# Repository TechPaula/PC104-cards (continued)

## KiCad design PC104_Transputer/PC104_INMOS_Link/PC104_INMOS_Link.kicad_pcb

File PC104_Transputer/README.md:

# PC104 Transputer card

This is a PC104plus board that provides a connection to an INMOS C011 and on to a transputer.
This is going to form the basis of a PC104 stack of transputers.

The PCI connector is not connected and is not needed, it is there so that should I get any PCI cards in the future I can use them on my system

TLDR; Currently none of these are proven beyond loopback tests

## Updates

2025-09-07 - Well the previous card had some issues, mostly around the address decoding as far as I can tell, so I made a new card with just the C011 on and added more of the ISA lines to the CPLD. This now behaves with both of my PC104 computers (the previous one would cause one of them to fail to boot). However all 4 of my TRAMs now seem to have stopped working :( The C011 link card does at least now perform loopback tests perfectly. The other thing I've done is cut the track from the ISA 14.3MHz clock and used the 8MHz bus clock. I need to update the schematics and PCB 

2025-07-19 - OMG, so much work... CPLD files updated and fixed a couple of errors. I can now write and read from 0x150 to 0x153 as expected. I can now also write to 0x160 & 0x161 as expected and get the behaviours expected. But when you read from 0x160 you got the wrong value and from then on when you read from 0x153 (output status) returns 0, so the output has not been sent/acknowledged by the TRAM.

### Some useful things I've discovered along the way;
* write a 1 to 0x160 Asserts reset, writing a 0 deasserts it.
* Write a 1 to 0x161 to asset Analyse, writing a 0 deasserts it
* Write a 0 to 0x152 to clear INPUT interrupt enable (unless you plan to use interrupts)
* Write a 0 to 0x152 to clear OUTPUT interrupt enable (unless you plan to use interrupts)
* READ from 0x152 to get the input status (if bit0 is 0 then there is no Data waiting)
* READ from 0x160 to get the error stats (if bit 0 is 0 then there is no error)
* Write to 0x151 to send data into the C011/TRAM.
* READ from 0x150 to receive data from the C011/TRAM

2025-07-11 - Spotted another mistake, I had the Databus reversed. I also added the CPLD files I've programmed and tested.

2025-07-09 - Spotted a major mistake with the CPLD, the board needs a redesign as it has the wrong pin out!

2025-07-06 - Fixed a few minor issues with both boards & added image of Dual TRAM board

2025-07-06 - Added TRAM model

2025-07-05 - Board routed but NOT yet built/tested, the code for the CPLD is not not written.

## License
There isn't one, if you want to build it or adapt it, go for it.
I offer no warranty, nor will I accept any responsiblity for damage to you or your equipment

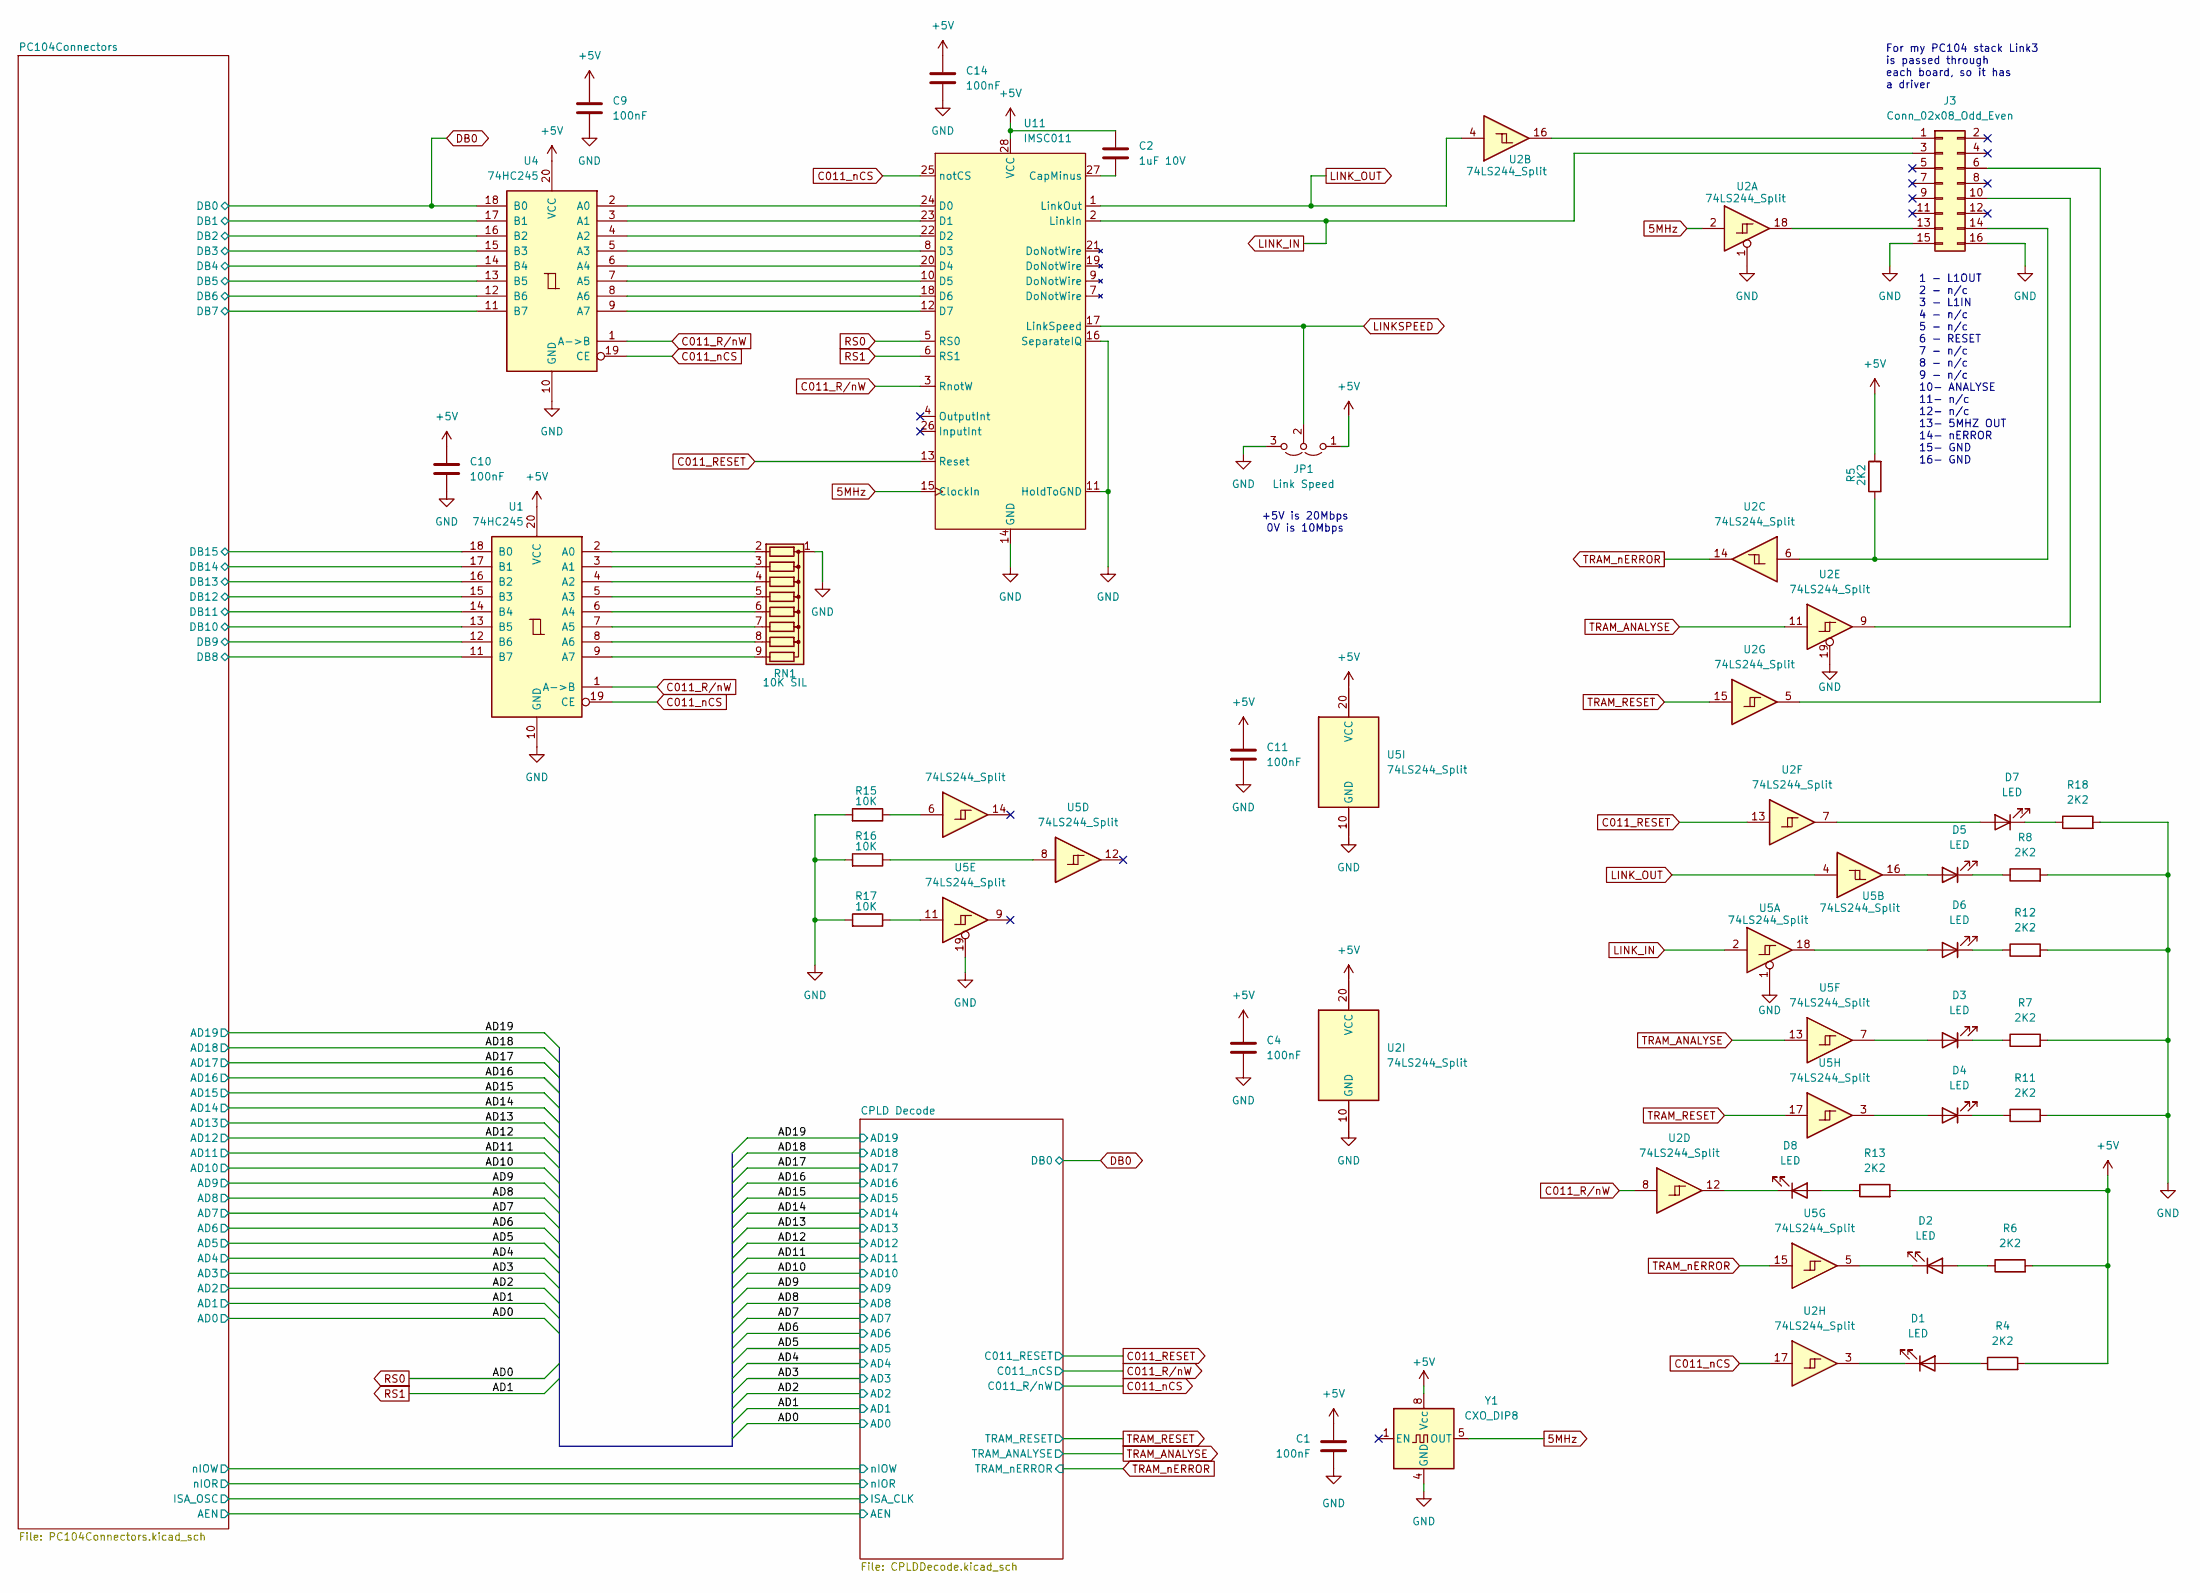
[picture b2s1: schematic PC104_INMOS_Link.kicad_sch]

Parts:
C1, C4, C9, C10, C11, C14: 100nF; C_0805_2012Metric
C2: 1uF 10V; C_0805_2012Metric
D1, D2, D3, D4, D5, D6, D7, D8: LED; LED_0603_1608Metric
J3: Conn_02x08_Odd_Even; PinHeader_2x08_P2.54mm_Horizontal
JP1: Link Speed; PinHeader_1x03_P2.54mm_Vertical
R4, R5, R6, R7, R8, R11, R12, R13, R18: 2K2; R_0603_1608Metric
R15, R16, R17: 10K; R_0603_1608Metric
RN1: 10K SIL; R_Array_SIP9
U1, U4: 74HC245; DIP-20_W7.62mm_Socket
U2, U5: 74LS244_Split; DIP-20_W7.62mm_Socket
U11: IMSC011; DIP-28_W15.24mm
Y1: CXO_DIP8; Oscillator_DIP-8

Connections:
5MHz: U2.2, U11.15 (ClockIn), Y1.5 (OUT)
+5V: C1.1, C2.1, C4.1, C9.1, C10.1, C11.1, C14.1, JP1.1 (A), R4.2, R5.2, R6.2, R13.2, U1.20 (VCC), U2.20 (VCC), U4.20 (VCC), U5.20 (VCC), U11.28 (VCC), Y1.8 (Vcc); also elsewhere on the board
/PC104Connectors/DB1: U4.17 (B1); also elsewhere on the board
/PC104Connectors/DB2: U4.16 (B2); also elsewhere on the board
/PC104Connectors/DB3: U4.15 (B3); also elsewhere on the board
/PC104Connectors/DB4: U4.14 (B4); also elsewhere on the board
/PC104Connectors/DB5: U4.13 (B5); also elsewhere on the board
/PC104Connectors/DB6: U4.12 (B6); also elsewhere on the board
/PC104Connectors/DB7: U4.11 (B7); also elsewhere on the board
/PC104Connectors/DB8: U1.11 (B7); also elsewhere on the board
/PC104Connectors/DB9: U1.12 (B6); also elsewhere on the board
/PC104Connectors/DB10: U1.13 (B5); also elsewhere on the board
/PC104Connectors/DB11: U1.14 (B4); also elsewhere on the board
/PC104Connectors/DB12: U1.15 (B3); also elsewhere on the board
/PC104Connectors/DB13: U1.16 (B2); also elsewhere on the board
/PC104Connectors/DB14: U1.17 (B1); also elsewhere on the board
/PC104Connectors/DB15: U1.18 (B0); also elsewhere on the board
C011_RESET: U2.13, U11.13 (Reset); also elsewhere on the board
C011_R/nW: U1.1 (A->B), U2.8, U4.1 (A->B), U11.3 (RnotW); also elsewhere on the board
C011_nCS: U1.19 (CE), U2.17, U4.19 (CE), U11.25 (notCS); also elsewhere on the board
DB0: U4.18 (B0); also elsewhere on the board
GND: C1.2, C4.2, C9.2, C10.2, C11.2, C14.2, J3.15, J3.16, JP1.3 (B), R7.2, R8.2, R11.2, R12.2, R15.2, R16.2, R17.2, R18.2, RN1.1 (common), U1.10 (GND), U2.1, U2.10 (GND), U2.19, U4.10 (GND), U5.1, U5.10 (GND), U5.19, U11.11 (HoldToGND), U11.14 (GND), U11.16 (SeparateIQ), Y1.4 (GND); also elsewhere on the board
LINKSPEED: JP1.2 (C), U11.17 (LinkSpeed)
LINK_IN: J3.3, U5.2, U11.2 (LinkIn)
LINK_OUT: U2.4, U5.4, U11.1 (LinkOut)
unnamed: D1.2 (A), R4.1
unnamed: D1.1 (K), U2.3
unnamed: D2.2 (A), R6.1
unnamed: D2.1 (K), U5.5
unnamed: D3.2 (A), U5.7
unnamed: D3.1 (K), R7.1
unnamed: D4.2 (A), U5.3
unnamed: D4.1 (K), R11.1
unnamed: D5.2 (A), U5.16
unnamed: D5.1 (K), R8.1
unnamed: D6.2 (A), U5.18
unnamed: D6.1 (K), R12.1
unnamed: D7.2 (A), U2.7
unnamed: D7.1 (K), R18.1
unnamed: D8.2 (A), R13.1
unnamed: D8.1 (K), U2.12
unnamed: J3.1, U2.16
unnamed: J3.6, U2.5
unnamed: J3.10, U2.9
unnamed: J3.13, U2.18
unnamed: J3.14, R5.1, U2.6
unnamed: R15.1, U5.6
unnamed: R16.1, U5.8
unnamed: R17.1, U5.11
unnamed: RN1.2 (R1), U1.2 (A0)
unnamed: RN1.3 (R2), U1.3 (A1)
unnamed: RN1.4 (R3), U1.4 (A2)
unnamed: RN1.5 (R4), U1.5 (A3)
unnamed: RN1.6 (R5), U1.6 (A4)
unnamed: RN1.7 (R6), U1.7 (A5)
unnamed: RN1.8 (R7), U1.8 (A6)
unnamed: RN1.9 (R8), U1.9 (A7)
unnamed: C2.2, U11.27 (CapMinus)
unnamed: U4.2 (A0), U11.24 (D0)
unnamed: U4.3 (A1), U11.23 (D1)
unnamed: U4.4 (A2), U11.22 (D2)
unnamed: U4.5 (A3), U11.8 (D3)
unnamed: U4.6 (A4), U11.20 (D4)
unnamed: U4.7 (A5), U11.10 (D5)
unnamed: U4.8 (A6), U11.18 (D6)
unnamed: U4.9 (A7), U11.12 (D7)
RS0: U11.5 (RS0); also elsewhere on the board
RS1: U11.6 (RS1); also elsewhere on the board
TRAM_ANALYSE: U2.11, U5.13; also elsewhere on the board
TRAM_RESET: U2.15, U5.17; also elsewhere on the board
TRAM_nERROR: U2.14, U5.15; also elsewhere on the board

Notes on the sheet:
For my PC104 stack Link3 is passed through each board, so it has a driver
1 - L1OUT 2 - n/c 3 - L1IN 4 - n/c 5 - n/c 6 - RESET 7 - n/c 8 - n/c 9 - n/c 10- ANALYSE 11- n/c 12- n/c 13- 5MHZ OUT 14- nERROR 15- GND 16- GND
+5V is 20Mbps 0V is 10Mbps

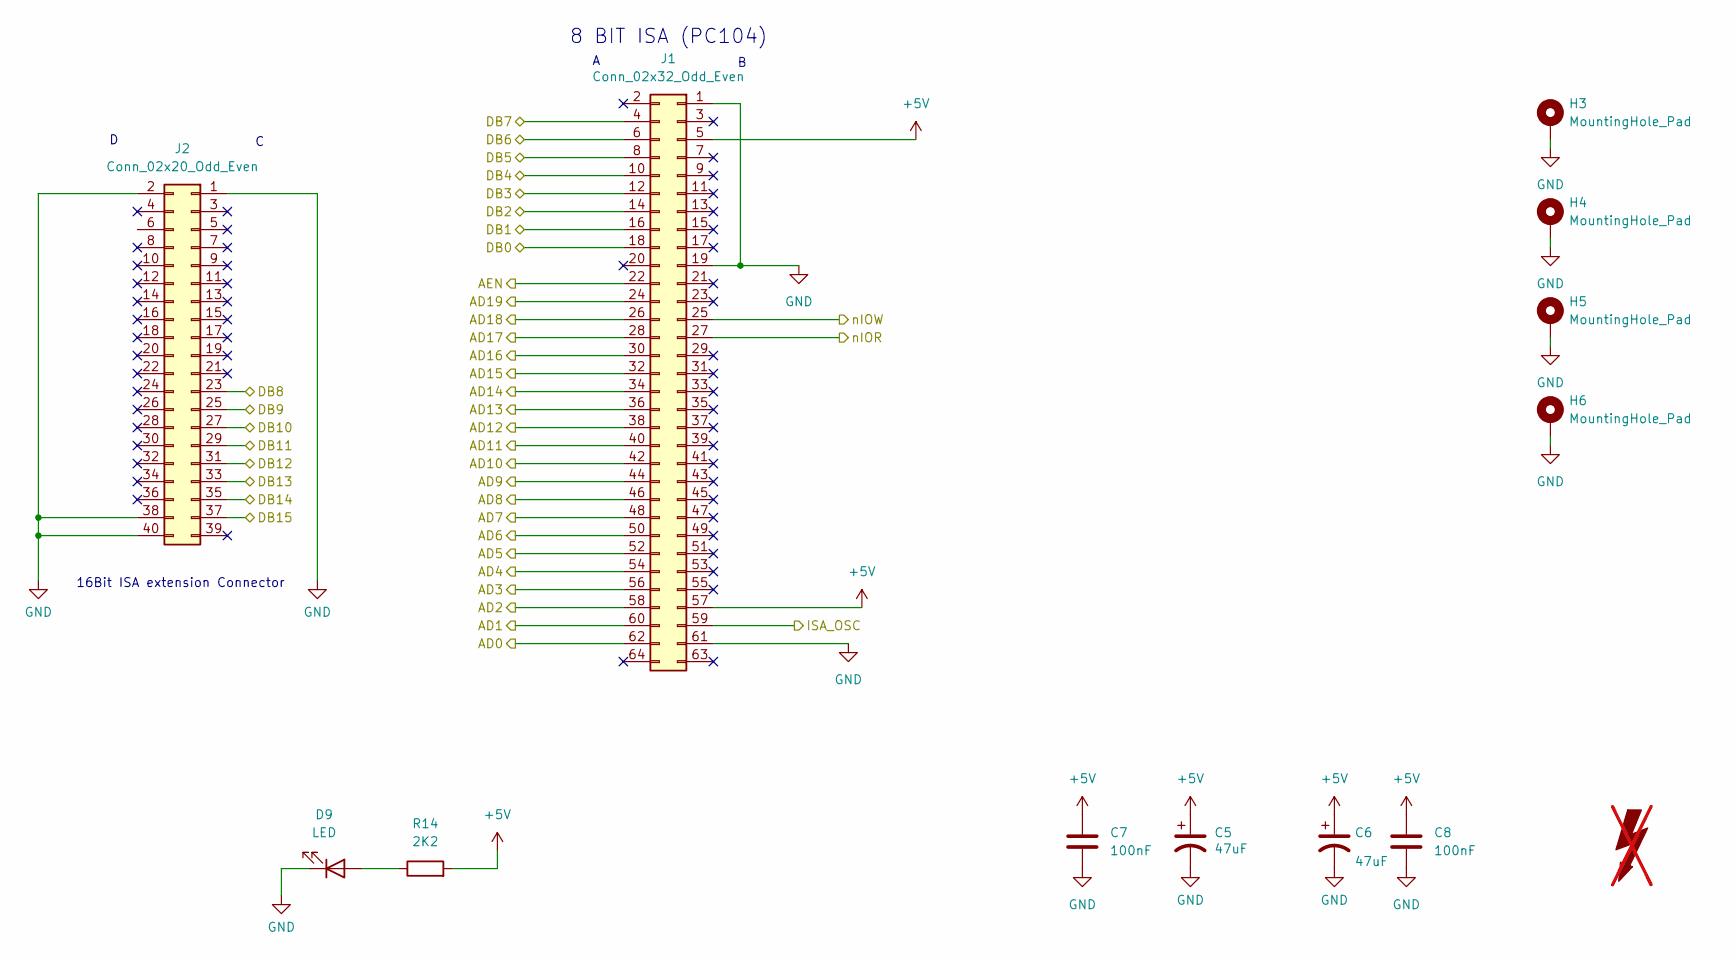
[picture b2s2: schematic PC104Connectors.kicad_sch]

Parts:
C5, C6: 47uF; C_1206_3216Metric; LCSC C96123
C7, C8: 100nF; C_0805_2012Metric
D9: LED; LED_0603_1608Metric
FOX1: SYM_Flash_Large; Fox_avatar_18mm; LCSC DNF; not fitted
H3, H4, H5, H6: MountingHole_Pad; MountingHole_3.2mm_M3_Pad_TopBottom; LCSC DNF
J1: Conn_02x32_Odd_Even; PinSocket_2x32_P2.54mm_Vertical; LCSC DNF
J2: Conn_02x20_Odd_Even; PinSocket_2x20_P2.54mm_Vertical; LCSC DNF
R14: 2K2; R_0603_1608Metric

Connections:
+5V: C5.1, C6.1, C7.1, C8.1, J1.5, J1.57, R14.2; also elsewhere on the board
/AD2: J1.58; also elsewhere on the board
/AD3: J1.56; also elsewhere on the board
/AD4: J1.54; also elsewhere on the board
/AD5: J1.52; also elsewhere on the board
/AD6: J1.50; also elsewhere on the board
/AD7: J1.48; also elsewhere on the board
/AD8: J1.46; also elsewhere on the board
/AD9: J1.44; also elsewhere on the board
/AD10: J1.42; also elsewhere on the board
/AD11: J1.40; also elsewhere on the board
/AD12: J1.38; also elsewhere on the board
/AD13: J1.36; also elsewhere on the board
/AD14: J1.34; also elsewhere on the board
/AD15: J1.32; also elsewhere on the board
/AD16: J1.30; also elsewhere on the board
/AD17: J1.28; also elsewhere on the board
/AD18: J1.26; also elsewhere on the board
/AD19: J1.24; also elsewhere on the board
/CPLD Decode/AEN: J1.22; also elsewhere on the board
/CPLD Decode/ISA_CLK: J1.59; also elsewhere on the board
/CPLD Decode/nIOR: J1.27; also elsewhere on the board
/CPLD Decode/nIOW: J1.25; also elsewhere on the board
/PC104Connectors/DB1: J1.16; also elsewhere on the board
/PC104Connectors/DB2: J1.14; also elsewhere on the board
/PC104Connectors/DB3: J1.12; also elsewhere on the board
/PC104Connectors/DB4: J1.10; also elsewhere on the board
/PC104Connectors/DB5: J1.8; also elsewhere on the board
/PC104Connectors/DB6: J1.6; also elsewhere on the board
/PC104Connectors/DB7: J1.4; also elsewhere on the board
/PC104Connectors/DB8: J2.23; also elsewhere on the board
/PC104Connectors/DB9: J2.25; also elsewhere on the board
/PC104Connectors/DB10: J2.27; also elsewhere on the board
/PC104Connectors/DB11: J2.29; also elsewhere on the board
/PC104Connectors/DB12: J2.31; also elsewhere on the board
/PC104Connectors/DB13: J2.33; also elsewhere on the board
/PC104Connectors/DB14: J2.35; also elsewhere on the board
/PC104Connectors/DB15: J2.37; also elsewhere on the board
DB0: J1.18; also elsewhere on the board
GND: C5.2, C6.2, C7.2, C8.2, D9.1 (K), H3.1, H4.1, H5.1, H6.1, J1.1, J1.19, J1.61, J2.1, J2.2, J2.38, J2.40; also elsewhere on the board
unnamed: D9.2 (A), R14.1
RS0: J1.62; also elsewhere on the board
RS1: J1.60; also elsewhere on the board

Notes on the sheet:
16Bit ISA extension Connector
8 BIT ISA (PC104)

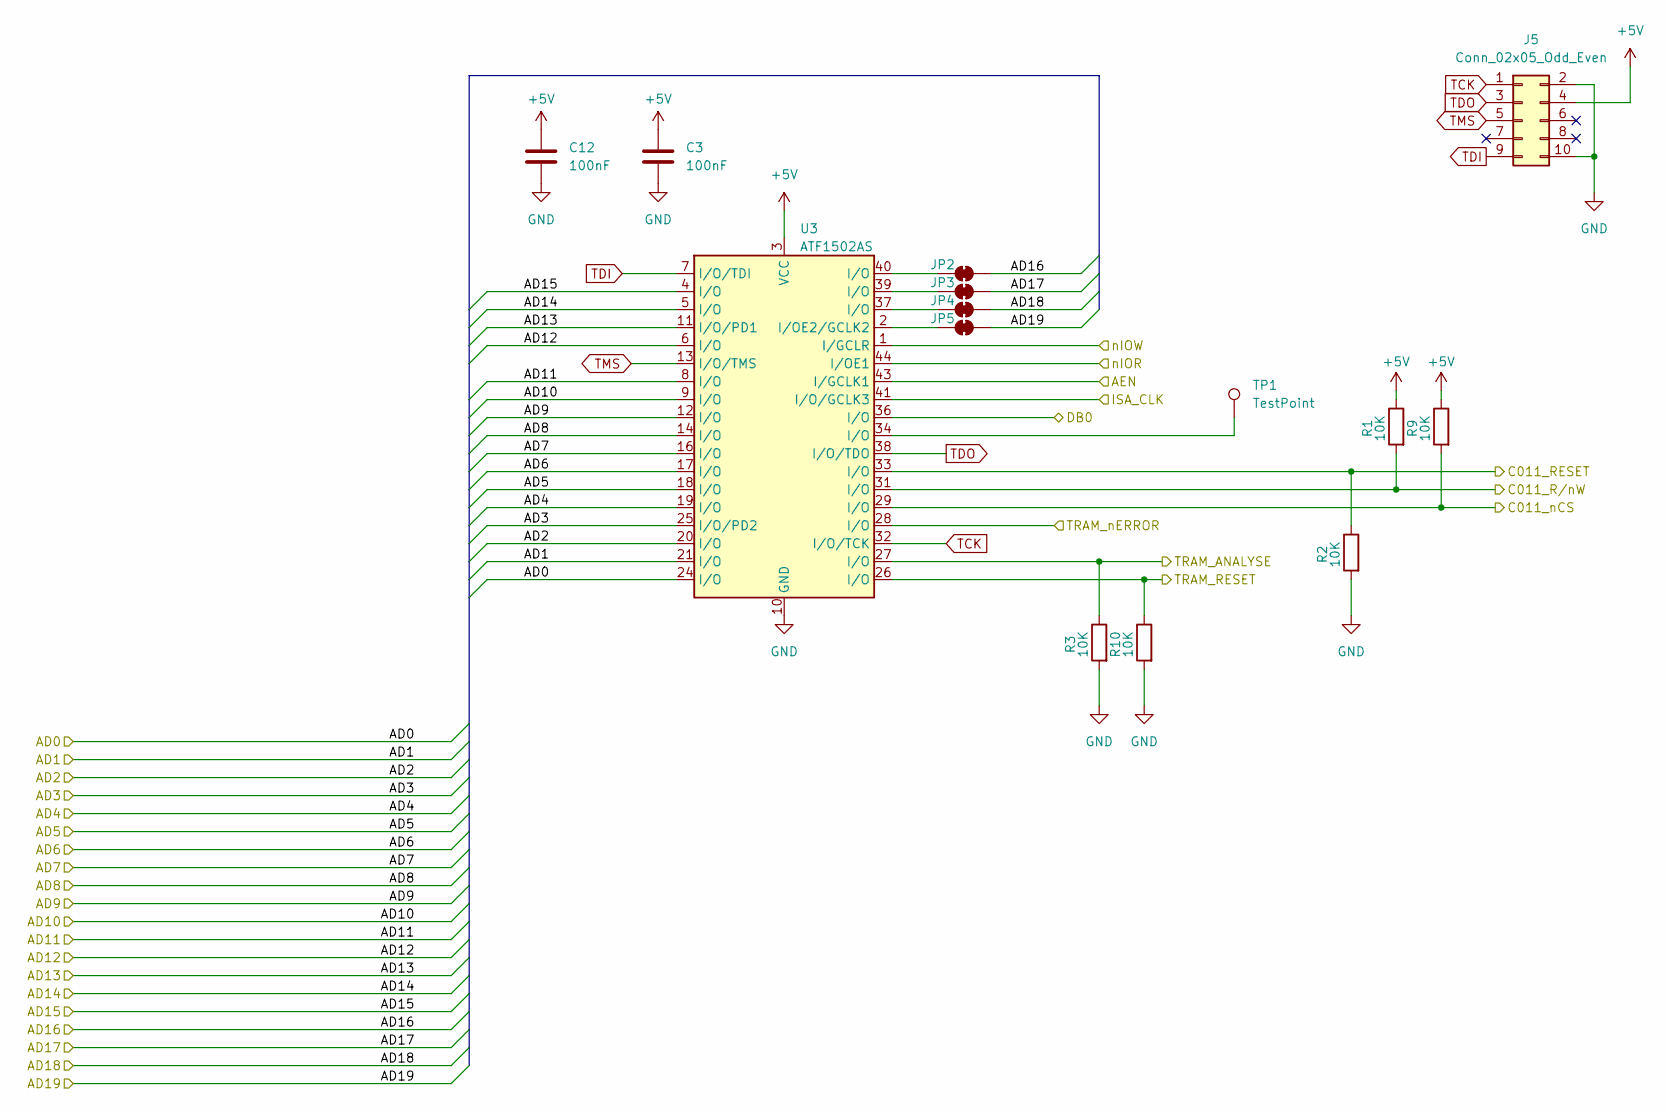
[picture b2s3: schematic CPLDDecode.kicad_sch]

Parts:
C3, C12: 100nF; C_0805_2012Metric
J5: Conn_02x05_Odd_Even; PinHeader_2x05_P2.54mm_Vertical
JP2, JP3, JP4, JP5: SolderJumper_2_Bridged; SolderJumper-2_P1.3mm_Bridged_RoundedPad1.0x1.5mm
R1, R2, R3, R9, R10: 10K; R_0603_1608Metric
TP1: TestPoint; TestPoint_Loop_D1.80mm_Drill1.0mm_Beaded
U3: ATF1502AS; PLCC-44_THT-Socket

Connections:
+5V: C3.1, C12.1, J5.4, R1.1, R9.1, U3.3 (VCC), U3.15 (VCC), U3.23 (VCC), U3.35 (VCC); also elsewhere on the board
/AD2: U3.20 (I/O); also elsewhere on the board
/AD3: U3.25 (I/O/PD2); also elsewhere on the board
/AD4: U3.19 (I/O); also elsewhere on the board
/AD5: U3.18 (I/O); also elsewhere on the board
/AD6: U3.17 (I/O); also elsewhere on the board
/AD7: U3.16 (I/O); also elsewhere on the board
/AD8: U3.14 (I/O); also elsewhere on the board
/AD9: U3.12 (I/O); also elsewhere on the board
/AD10: U3.9 (I/O); also elsewhere on the board
/AD11: U3.8 (I/O); also elsewhere on the board
/AD12: U3.6 (I/O); also elsewhere on the board
/AD13: U3.11 (I/O/PD1); also elsewhere on the board
/AD14: U3.5 (I/O); also elsewhere on the board
/AD15: U3.4 (I/O); also elsewhere on the board
/AD16: JP2.2 (B); also elsewhere on the board
/AD17: JP3.2 (B); also elsewhere on the board
/AD18: JP4.2 (B); also elsewhere on the board
/AD19: JP5.2 (B); also elsewhere on the board
/CPLD Decode/AEN: U3.43 (I/GCLK1); also elsewhere on the board
/CPLD Decode/ISA_CLK: U3.41 (I/O/GCLK3); also elsewhere on the board
/CPLD Decode/nIOR: U3.44 (I/OE1); also elsewhere on the board
/CPLD Decode/nIOW: U3.1 (I/GCLR); also elsewhere on the board
C011_RESET: R2.1, U3.33 (I/O); also elsewhere on the board
C011_R/nW: R9.2, U3.29 (I/O); also elsewhere on the board
C011_nCS: R1.2, U3.31 (I/O); also elsewhere on the board
DB0: U3.36 (I/O); also elsewhere on the board
GND: C3.2, C12.2, J5.2, J5.10, R2.2, R3.2, R10.2, U3.10 (GND), U3.22 (GND), U3.30 (GND), U3.42 (GND); also elsewhere on the board
unnamed: JP2.1 (A), U3.40 (I/O)
unnamed: JP3.1 (A), U3.39 (I/O)
unnamed: JP4.1 (A), U3.37 (I/O)
unnamed: JP5.1 (A), U3.2 (I/OE2/GCLK2)
unnamed: TP1.1, U3.34 (I/O)
RS0: U3.24 (I/O); also elsewhere on the board
RS1: U3.21 (I/O); also elsewhere on the board
TCK: J5.1, U3.32 (I/O/TCK)
TDI: J5.9, U3.7 (I/O/TDI)
TDO: J5.3, U3.38 (I/O/TDO)
TMS: J5.5, U3.13 (I/O/TMS)
TRAM_ANALYSE: R3.1, U3.27 (I/O); also elsewhere on the board
TRAM_RESET: R10.1, U3.26 (I/O); also elsewhere on the board
TRAM_nERROR: U3.28 (I/O); also elsewhere on the board

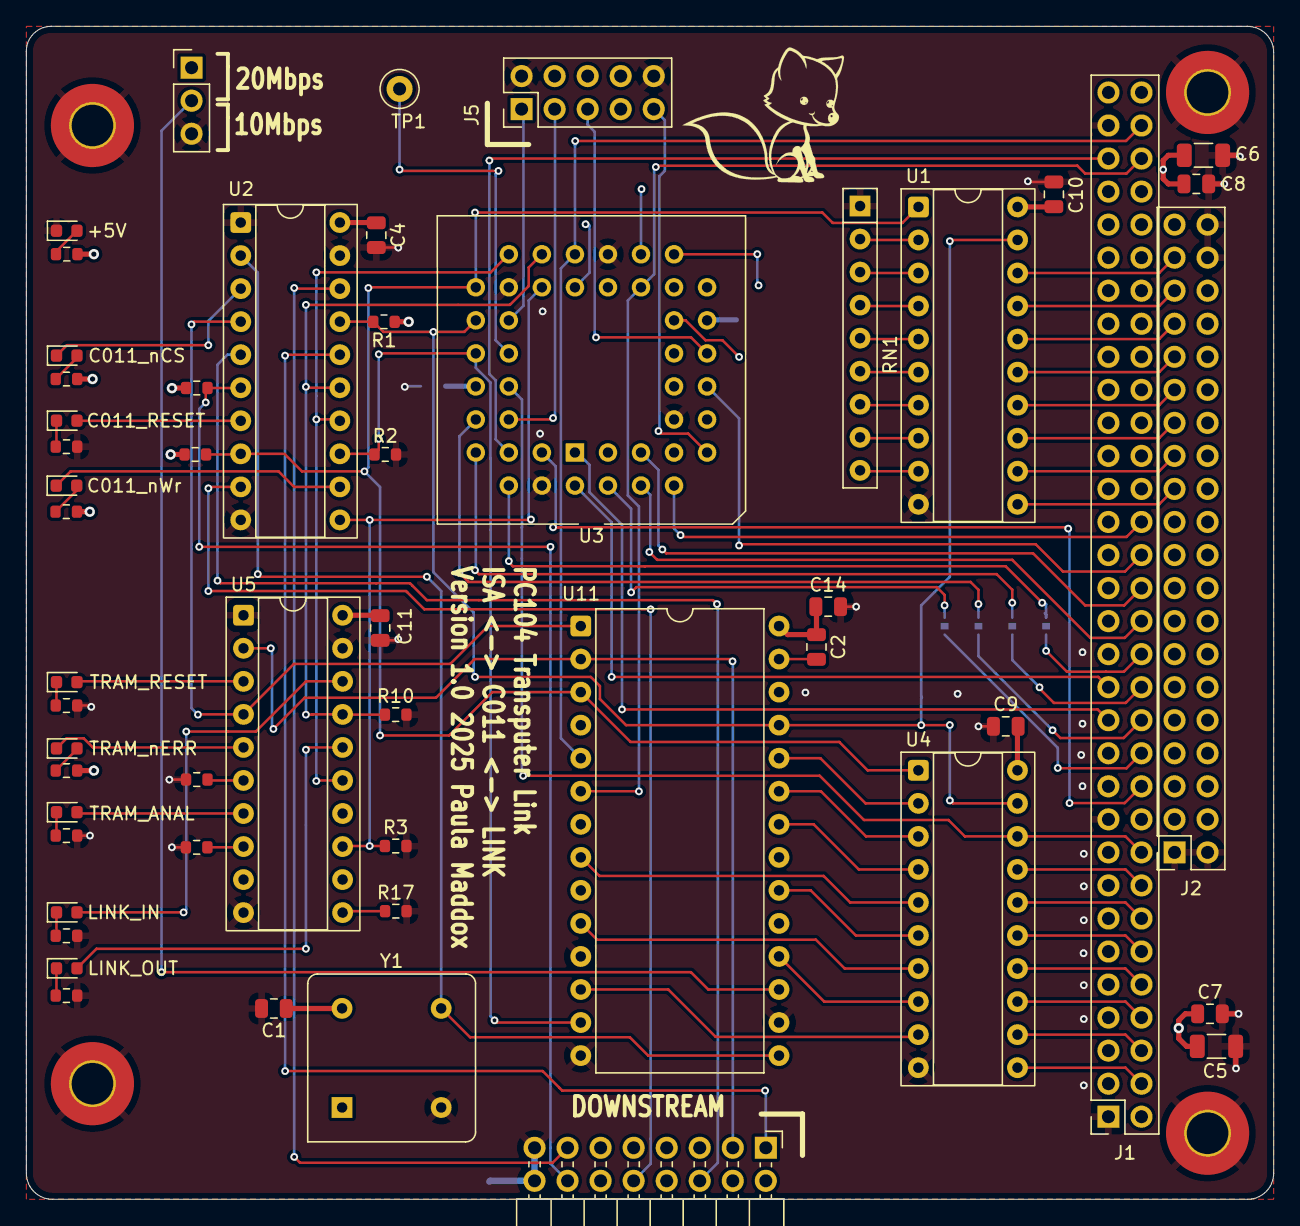
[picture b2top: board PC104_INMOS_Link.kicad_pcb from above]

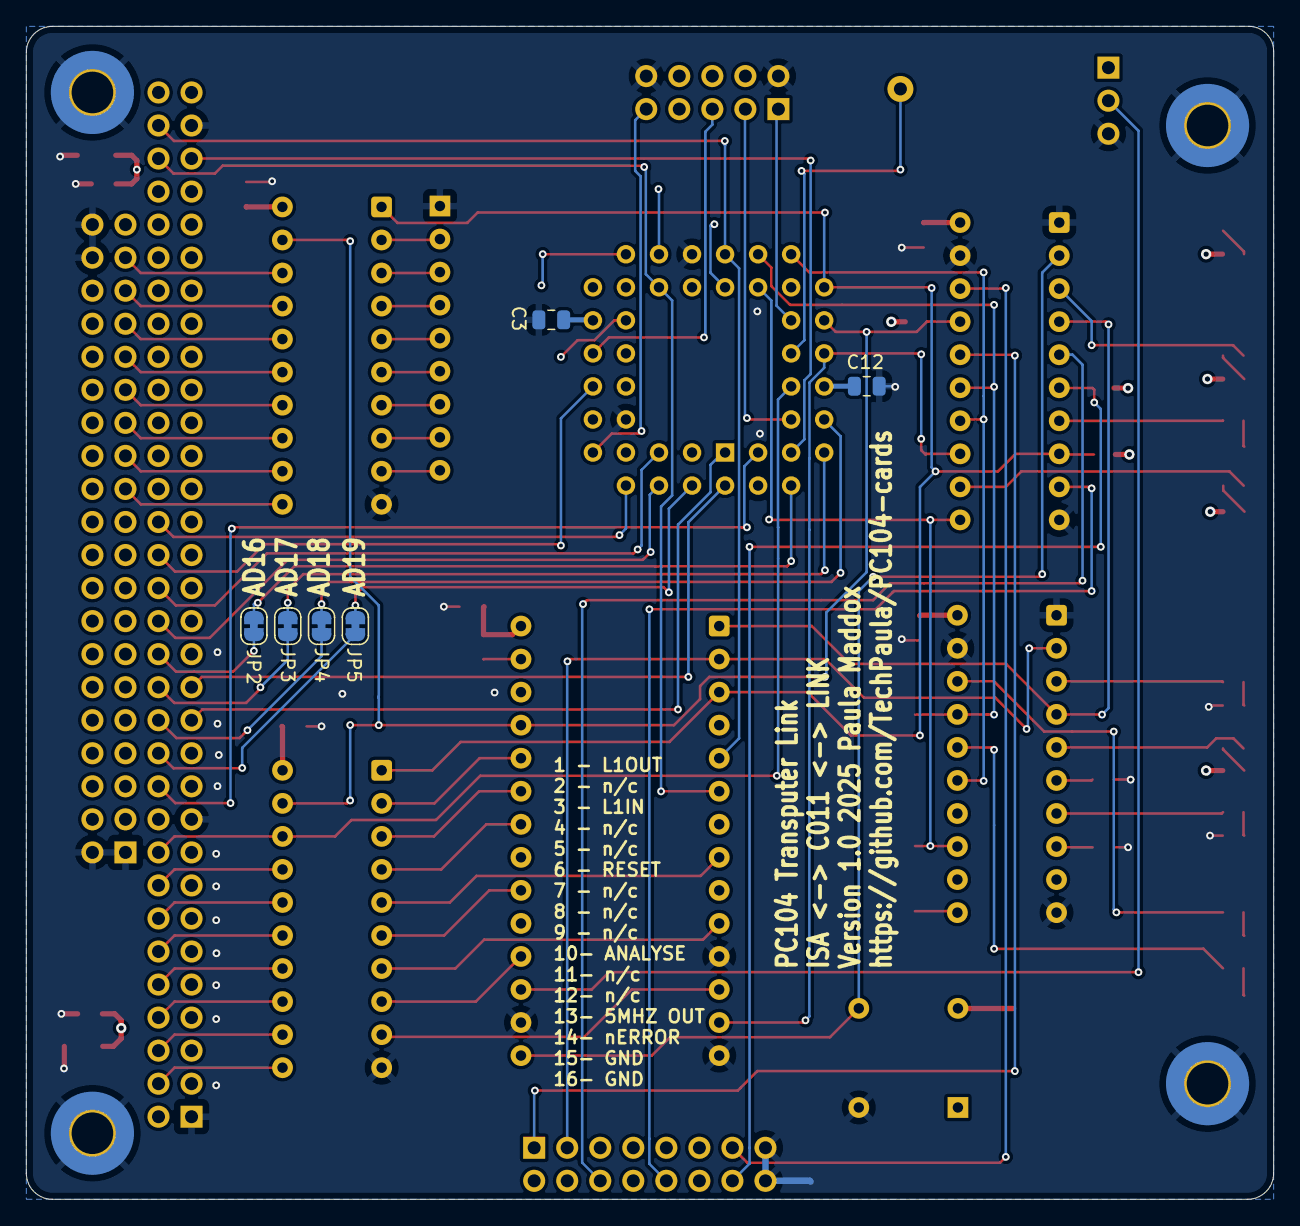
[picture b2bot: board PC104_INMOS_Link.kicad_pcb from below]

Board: 4 copper layers, 95.9 x 90.2 mm, 63 parts (6 on the bottom side), 103 nets.

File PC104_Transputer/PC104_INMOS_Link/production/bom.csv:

Designator,Footprint,Quantity,Value,LCSC Part #
"C1, C10, C11, C12, C14, C3, C4, C7, C8, C9",0805,10,100nF,
C2,0805,1,1uF 10V,
"C5, C6",1206,2,47uF,C96123
"D1, D2, D3, D4, D5, D6, D7, D8, D9",0603,9,LED,
FOX1,Fox_avatar_18mm,1,SYM_Flash_Large,DNF
"H3, H4, H5, H6",MountingHole_3.2mm_M3_Pad_TopBottom,4,MountingHole_Pad,DNF
J1,PinSocket_2x32_P2.54mm_Vertical,1,Conn_02x32_Odd_Even,DNF
J2,PinSocket_2x20_P2.54mm_Vertical,1,Conn_02x20_Odd_Even,DNF
J3,PinHeader_2x08_P2.54mm_Horizontal,1,Conn_02x08_Odd_Even,
J5,PinHeader_2x05_P2.54mm_Vertical,1,Conn_02x05_Odd_Even,
"R1, R10, R15, R16, R17, R2, R3, R9",0603,8,10K,
"R11, R12, R13, R14, R18, R4, R5, R6, R7, R8",0603,10,2K2,
RN1,R_Array_SIP9,1,10K SIL,
TP1,TestPoint_Loop_D1.80mm_Drill1.0mm_Beaded,1,TestPoint,
"U1, U4",DIP-20_W7.62mm_Socket,2,74HC245,
U11,DIP-28_W15.24mm,1,IMSC011,
"U2, U5",DIP-20_W7.62mm_Socket,2,74LS244_Split,
U3,PLCC-44_THT-Socket,1,ATF1502AS,
Y1,Oscillator_DIP-8,1,CXO_DIP8,
